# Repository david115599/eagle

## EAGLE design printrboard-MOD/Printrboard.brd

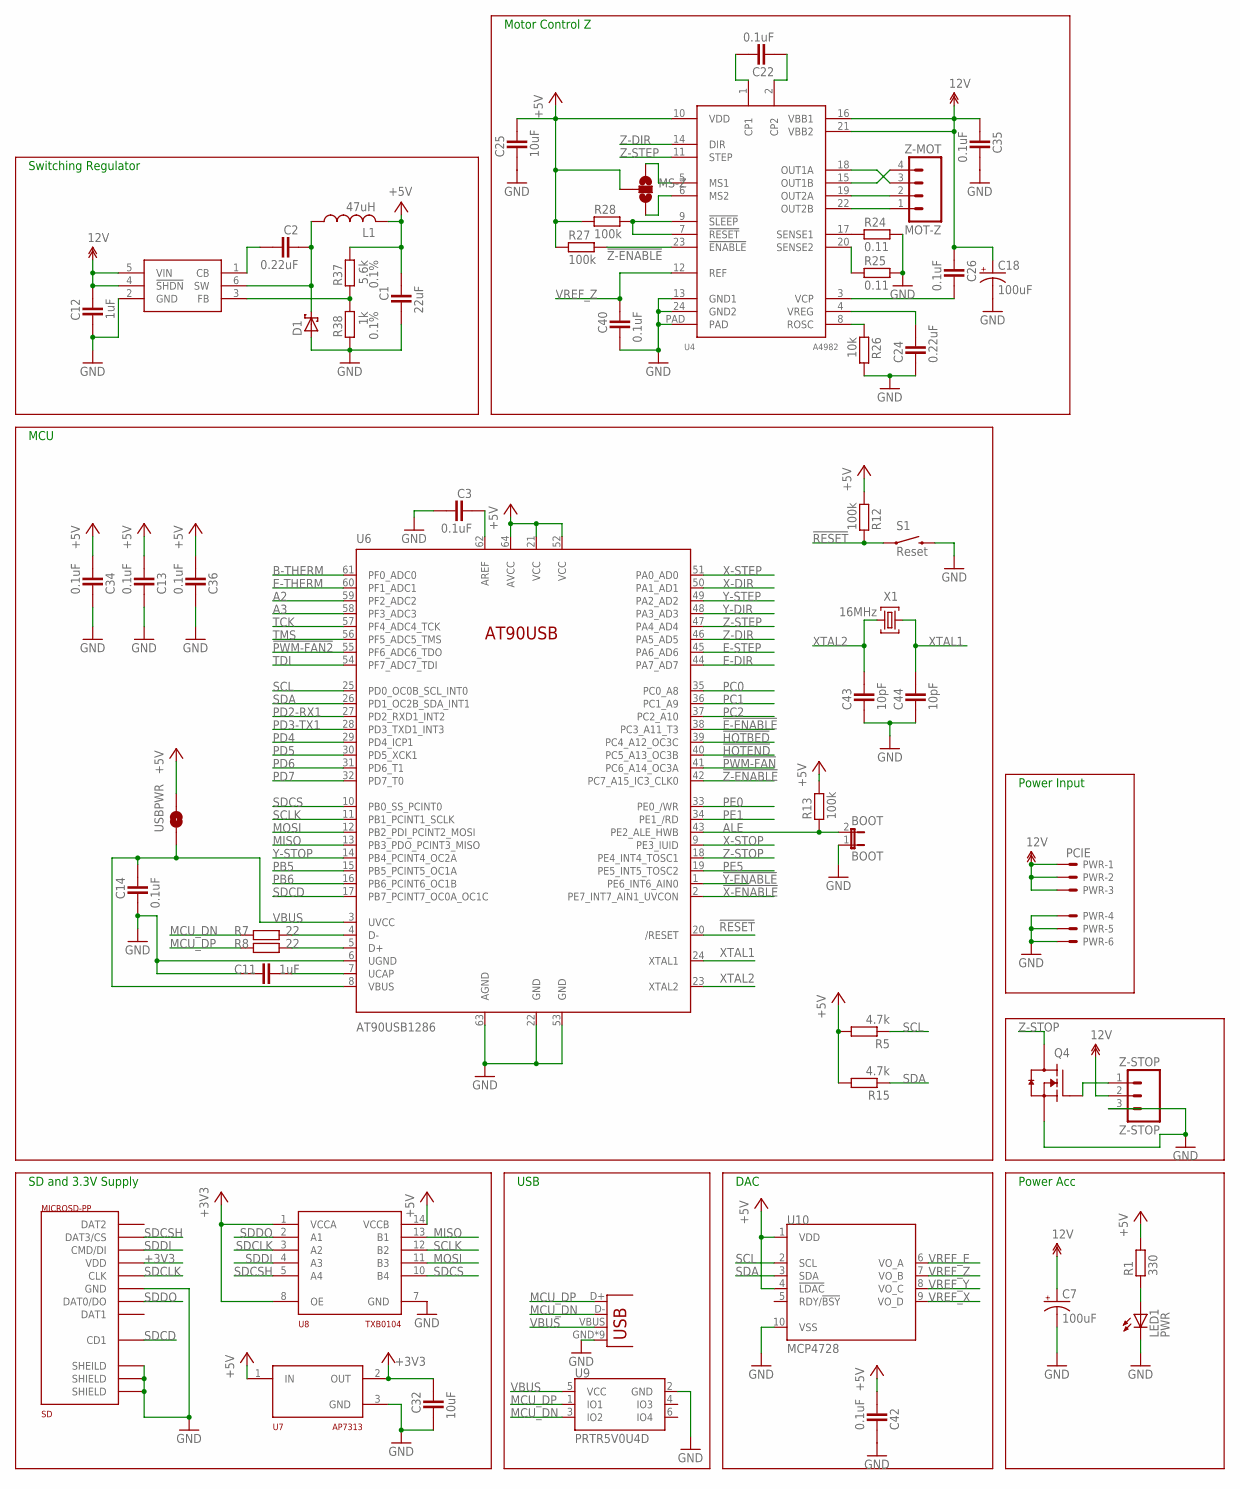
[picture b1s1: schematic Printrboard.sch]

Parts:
BOOT: BOOT; 1X02; MPN 640452-2
C1: 22uF; CAPC2012X145AN; MPN GRT21BR60J226ME13L
C2, C24: 0.22uF; CAPC2012X145AN
C3, C13, C14, C22, C26, C34, C35, C36, C40, C42: 0.1uF; CAPC2012X145AN
C7, C18: 100uF; PANASONIC_D
C11, C12: 1uF; CAPC2012X145AN
C25, C32: 10uF; CAPC2012X145AN
C43, C44: 10pF; CAPC2012X145AN
D1: SCH-DIODESMA; SMA
L1: 47uH; SDR1006
LED1: PWR; CHIP-LED0805
MS-Z: SOLDERJUMPER_2WAYCONNECTED; SJ_3_CONNECTED
PWR: PCIE; 5566-6
Q4: RFP30N06LE; SOT95P280X135-3N
R1: 330; RESC2012X70N
R5, R15: 4.7k; RESC2012X70N
R7, R8: 22; RESC2012X70N
R12, R13, R27, R28: 100k; RESC2012X70N
R24, R25: 0.11; RESC2012X70N
R26: 10k; RESC2012X70N
R37: 5.6k; RESC2012X70N; TOLERANCE 0.1%
R38: 1k; RESC2012X70N; TOLERANCE 0.1%
S1: Reset; TACTILE_SWITCH_TALL
SD: MICROSD-PP; USD-101-00660-68-6
U1: LM2841; TSOT6
U4: A4982; TSSOP-24
U6: AT90USB1286; TQFP64-2
U7: AP7313; SOT23C
U8: TXB0104; TSSOP14
U9: PRTR5V0U4D; SOT23-6
U10: MCP4728; MSOP10
USB-M: USB-MICRO-PTH; USB-MICROB-PTH
USBPWR: SOLDERJUMPERNO; SJ_2S-NO
X1: 16MHz; NDK-XTAL
Z-MOT: MOT-Z; MOLEX-1X4
Z-STOP: Z-STOP; MOLEX-1X3

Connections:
12V: C7.+, C12.1, C18.+, C26.1, C35.1, PWR.1, PWR.2, PWR.3, U1.4 (!SHDN), U1.5 (VIN), U4.16 (VBB1), U4.21 (VBB2), Z-STOP.2
!E-ENABLE: U6.38 (PC3_A11_T3)
!HOTBED: U6.39 (PC4_A12_OC3C)
!HOTEND: U6.40 (PC5_A13_OC3B)
!PWM-FAN: U6.41 (PC6_A14_OC3A)
!PWM-FAN2: U6.55 (PF6_ADC6_TDO)
!RESET: R12.1, S1.A2 (1), U6.20 (/RESET)
!X-ENABLE: U6.2 (PE7_INT7_AIN1_UVCON)
!Y-ENABLE: U6.1 (PE6_INT6_AIN0)
!Z-ENABLE: R27.2, U4.23 (!ENABLE), U6.42 (PC7_A15_IC3_CLK0)
+3V3: C32.1, SD.P$4 (VDD), U7.2 (OUT), U8.1 (VCCA), U8.8 (OE)
+5V: C1.1, C13.2, C25.2, C34.2, C36.2, C42.2, L1.P$2 (2), MS-Z.2, R1.2, R5.2, R12.2, R13.2, R15.2, R27.1, R28.1, R37.1, U4.10 (VDD), U6.21 (VCC), U6.52 (VCC), U6.64 (AVCC), U7.1 (IN), U8.14 (VCCB), U10.1 (VDD), U10.4 (!LDAC), USBPWR.2
A2: U6.59 (PF2_ADC2)
A3: U6.58 (PF3_ADC3)
ALE: BOOT.2, R13.1, U6.43 (PE2_ALE_HWB)
AREF: C3.1, U6.62 (AREF)
B-THERM: U6.61 (PF0_ADC0)
E-DIR: U6.44 (PA7_AD7)
E-STEP: U6.45 (PA6_AD6)
E-THERM: U6.60 (PF1_ADC1)
GND: BOOT.1, C1.2, C3.2, C7.-, C11.1, C12.2, C13.1, C14.2, C18.-, C24.1, C25.1, C32.2, C34.1, C35.2, C36.1, C40.2, C42.1, C43.1, C44.1, D1.A, LED1.C, PWR.4, PWR.5, PWR.6, Q4.2 (S), R24.2, R25.2, R26.2, R38.2, S1.B2 (2), SD.GND1 (SHEILD), SD.GND2 (SHIELD), SD.GND3 (SHIELD), SD.P$6 (GND), U1.2 (GND), U4.13 (GND1), U4.24 (GND2), U4.PAD, U6.6 (UGND), U6.22 (GND), U6.53 (GND), U6.63 (AGND), U7.3 (GND), U8.7 (GND), U9.2 (GND), U10.10 (VSS), USB-M.GND, USB-M.GND1 (GND), USB-M.GND2 (GND), USB-M.GND3 (GND), USB-M.GND4 (GND), USB-M.GND5 (GND), USB-M.GND6 (GND), USB-M.GND7 (GND), USB-M.GND8 (GND), Z-STOP.3
MCU_DN: R7.1, U9.3 (IO2), USB-M.D-
MCU_DP: R8.1, U9.1 (IO1), USB-M.D+
MISO: U6.13 (PB3_PDO_PCINT3_MISO), U8.13 (B1)
MOSI: U6.12 (PB2_PDI_PCINT2_MOSI), U8.11 (B3)
unnamed: LED1.A, R1.1
unnamed: R7.2, U6.4 (D-)
unnamed: R8.2, U6.5 (D+)
unnamed: Q4.1 (G), Z-STOP.1
unnamed: C11.2, U6.7 (UCAP)
unnamed: R37.2, R38.1, U1.3 (FB)
unnamed: U4.15 (OUT1B), Z-MOT.4
unnamed: U4.18 (OUT1A), Z-MOT.3
unnamed: U4.19 (OUT2A), Z-MOT.2
unnamed: C22.2, U4.1 (CP1)
unnamed: C22.1, U4.2 (CP2)
unnamed: R24.1, U4.17 (SENSE1)
unnamed: R25.1, U4.20 (SENSE2)
unnamed: R26.1, U4.8 (ROSC)
unnamed: C24.2, U4.4 (VREG)
unnamed: R28.2, U4.7 (!RESET), U4.9 (!SLEEP)
unnamed: C26.2, U4.3 (VCP)
unnamed: U4.22 (OUT2B), Z-MOT.1
unnamed: MS-Z.1, U4.5 (MS1)
unnamed: MS-Z.3, U4.6 (MS2)
unnamed: C2.1, D1.C, L1.P$1 (1), U1.6 (SW)
unnamed: C2.2, U1.1 (CB)
PB5: U6.15 (PB5_PCINT5_OC1A)
PB6: U6.16 (PB6_PCINT6_OC1B)
PC0: U6.35 (PC0_A8)
PC1: U6.36 (PC1_A9)
PC2: U6.37 (PC2_A10)
PD2-RX1: U6.27 (PD2_RXD1_INT2)
PD3-TX1: U6.28 (PD3_TXD1_INT3)
PD4: U6.29 (PD4_ICP1)
PD5: U6.30 (PD5_XCK1)
PD6: U6.31 (PD6_T1)
PD7: U6.32 (PD7_T0)
PE0: U6.33 (PE0_/WR)
PE1: U6.34 (PE1_/RD)
PE5: U6.19 (PE5_INT5_TOSC2)
SCL: R5.1, U6.25 (PD0_OC0B_SCL_INT0), U10.2 (SCL)
SCLK: U6.11 (PB1_PCINT1_SCLK), U8.12 (B2)
SDA: R15.1, U6.26 (PD1_OC2B_SDA_INT1), U10.3 (SDA)
SDCD: SD.CD (CD1), U6.17 (PB7_PCINT7_OC0A_OC1C)
SDCLK: SD.P$5 (CLK), U8.3 (A2)
SDCS: U6.10 (PB0_SS_PCINT0), U8.10 (B4)
SDCSH: SD.P$2 (DAT3/CS), U8.5 (A4)
SDDI: SD.P$3 (CMD/DI), U8.4 (A3)
SDDO: SD.P$7 (DAT0/DO), U8.2 (A1)
TCK: U6.57 (PF4_ADC4_TCK)
TDI: U6.54 (PF7_ADC7_TDI)
TMS: U6.56 (PF5_ADC5_TMS)
VBUS: C14.1, U6.3 (UVCC), U6.8 (VBUS), U9.5 (VCC), USB-M.VBUS, USBPWR.1
VREF_E: U10.6 (VO_A)
VREF_X: U10.9 (VO_D)
VREF_Y: U10.8 (VO_C)
VREF_Z: C40.1, U4.12 (REF), U10.7 (VO_B)
X-DIR: U6.50 (PA1_AD1)
X-STEP: U6.51 (PA0_AD0)
X-STOP: U6.9 (PE3_IUID)
XTAL1: C44.2, U6.24 (XTAL1), X1.P$1 (1)
XTAL2: C43.2, U6.23 (XTAL2), X1.P$2 (2)
Y-DIR: U6.48 (PA3_AD3)
Y-STEP: U6.49 (PA2_AD2)
Y-STOP: U6.14 (PB4_PCINT4_OC2A)
Z-DIR: U4.14 (DIR), U6.46 (PA5_AD5)
Z-STEP: U4.11 (STEP), U6.47 (PA4_AD4)
Z-STOP: Q4.3 (D), U6.18 (PE4_INT4_TOSC1)

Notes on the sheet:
Motor Control Z
Power Acc
Switching Regulator
SD and 3.3V Supply
Power Input
MCU
USB
DAC

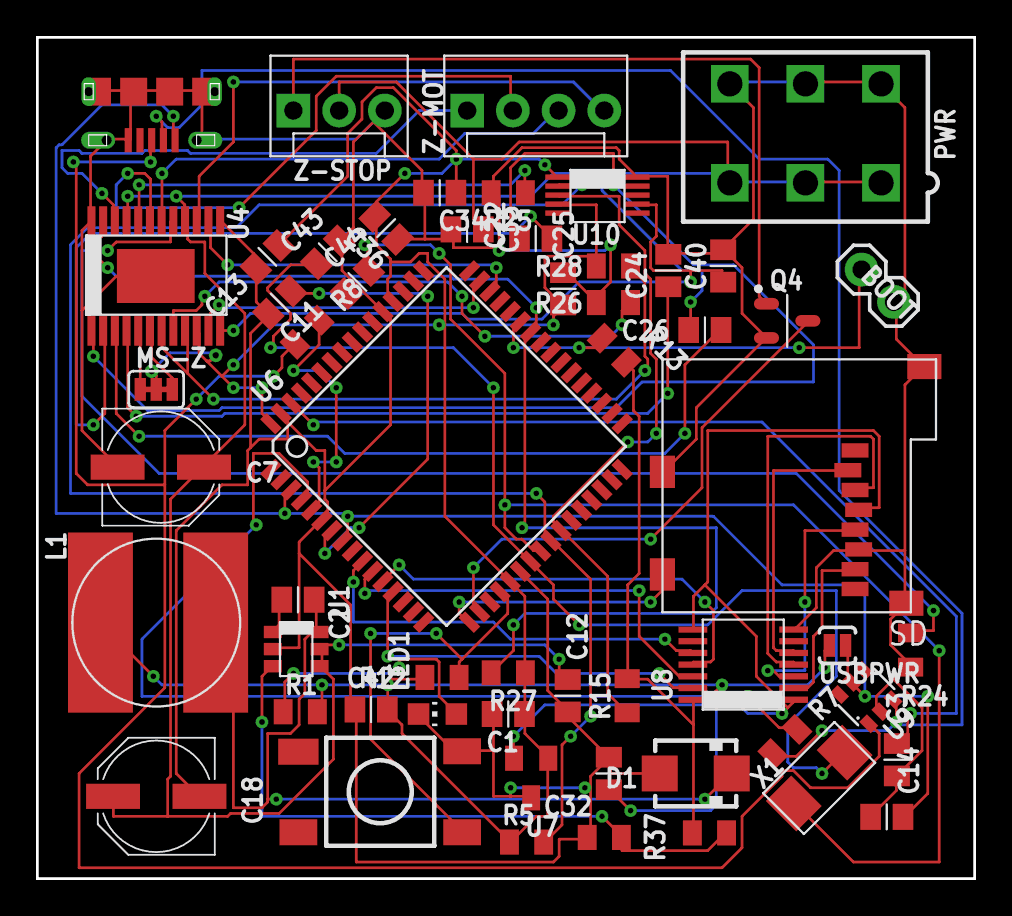
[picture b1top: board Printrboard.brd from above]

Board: 4 copper layers, 52.1 x 46.7 mm, 56 parts (0 on the bottom side), 50 nets.

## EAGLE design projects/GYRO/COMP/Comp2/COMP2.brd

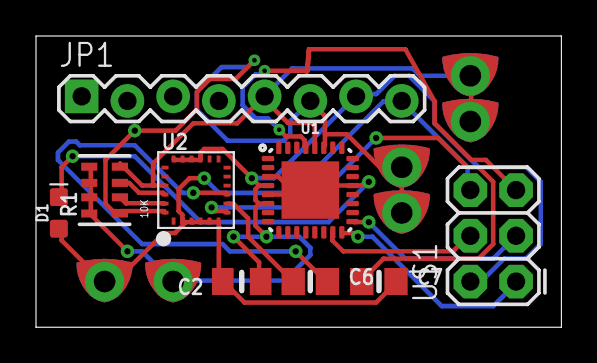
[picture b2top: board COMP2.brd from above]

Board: 2 copper layers, 29.2 x 16.2 mm, 15 parts (0 on the bottom side), 14 nets.

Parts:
C2: 10µF; 0805_10MGAP
C6: 0.22uF; 0805-NO
C7: 10uF; 0805-NO
D1: BLUE; LED-0603
GND: SEWTAP0.5IN; SEWINGTAP_0.5
JP1: 1X08_LOCK
R1: 10K; RESPACK_4X0603
SCL1, SCL2: SEWTAP0.5IN; SEWINGTAP_0.5
SDA1, SDA2: SEWTAP0.5IN; SEWINGTAP_0.5
U1: MLF32-PAD
U2: LSM9DS0TR; LGA24_4X4MM
U$1: AVR_SPI_PRG_6PTH; 2X3
VCC: SEWTAP0.5IN; SEWINGTAP_0.5

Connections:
GND: C2.2, C7.2, D1.A, GND.TAP, JP1.8, U2.2, U2.3, U2.4, U2.5, U2.6, U$1.6
MISO: U1.16, U$1.1
MOSI: U1.15, U$1.4
unnamed: C6.1, U2.8
unnamed: C6.2, U2.9
unnamed: D1.C, U1.3, U1.5, U1.21, U1.PAD
unnamed: C7.1, U2.7
RESET: U1.29, U$1.5
SA0_G: R1.3, U2.22
SA0_XM: R1.2, U2.23
SCK: U1.17, U$1.3
SCL: JP1.5, R1.4, SCL1.TAP, SCL2.TAP, U1.28, U2.21
SDA: JP1.6, R1.1, SDA1.TAP, SDA2.TAP, U1.27, U2.24
VCC: C2.1, JP1.7, R1.5, R1.6, R1.7, R1.8, U1.4, U1.6, U2.15, U2.16, U2.17, U2.18, U$1.2, VCC.TAP

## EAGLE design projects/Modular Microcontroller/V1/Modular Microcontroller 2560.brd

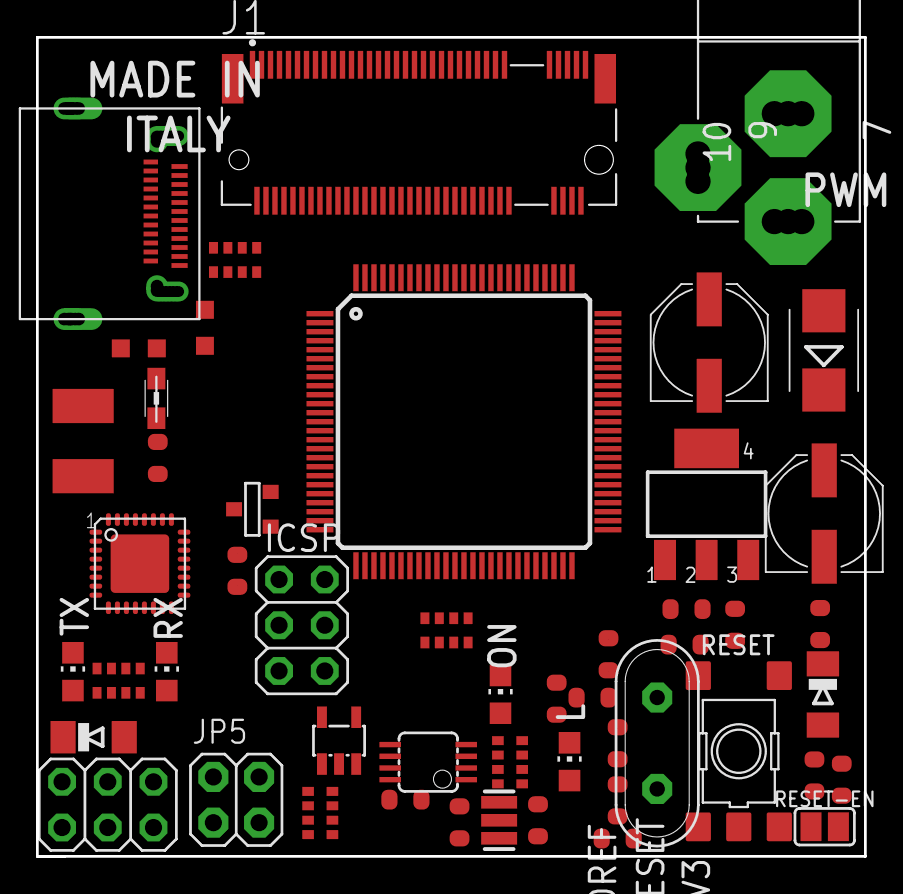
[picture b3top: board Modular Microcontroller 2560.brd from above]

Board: 2 copper layers, 46.0 x 45.5 mm, 52 parts (1 on the bottom side), 48 nets, no tracks yet.

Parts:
C1, C14, C15: 22p; C0603-ROUND
C2, C3, C4, C5, C6, C7, C8, C9, C11, C12: 100n; C0603-ROUND
C10, C13: 1u; C0603-ROUND
D1: M7; SMB
D2, D3: CD1206-S01575; MINIMELF
F1: MF-MSMF050-2 500mA; L1812
GROUND: SJ
IC1: NCP1117ST50T3G; SOT223
IC3: ATMEGA2560-16AU; TQFP100
IC4: ATMEGA16U2-MU; MLF32
IC6: LP2985-33DBVR; SOT23-DBV
IC7: LMV358IDGKR; MSOP08
ICSP, ICSP1: 3x2M; 2X03
J1: 1-2199119-3; TE_1-2199119-3
JP5: 2x2M - NM; 2X02
L: YELLOW; CHIP-LED0805
L1: BLM21; 0805
ON: GREEN; CHIP-LED0805
PC1, PC2: 47u; PANASONIC_D
R1, R2: 1M; R0603-ROUND
RESET: TS42031-160R-TR-7260; TS42
RESET-EN: SJ
RN1, RN5: 10K; CAT16
RN2: 22R; CAY16
RN3, RN4: 1k; CAY16
RX: YELLOW; CHIP-LED0805
T1: FDN340P; SOT-23
TX: YELLOW; CHIP-LED0805
U$2: USB-TYPE-C; USB-TYPE-C-SMT
X1: POWERSUPPLY_DC21MMX; POWERSUPPLY_DC-21MM
Y1: CSTCE16M0V53-R0 16MHZ; RESONATOR
Y2: 16MHz; QS
Z1, Z2: CG0603MLC-05E; CT/CN0603

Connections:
8PB4: IC4.18, JP5.1
8PB5: IC4.19, JP5.3
8PB6: IC4.20, JP5.2
8PB7: IC4.21, JP5.4
+3V3: C13.2, IC6.5, IC7.6
+5V: C4.1, C5.1, C6.1, C9.1, C11.2, D2.C, D3.C, IC1.2, IC1.4, IC3.10, IC3.31, IC3.61, IC3.80, IC3.100, IC4.4, IC4.32, IC6.1, IC6.3, IC7.8, ICSP.2, ICSP1.2, PC2.+, RN1.6, RN1.7, RN3.1, RN4.5, RN4.6, RN5.2, RN5.8, T1.2
AREF: C3.1, IC3.98
CMP: C12.2, IC7.5, RN5.3, RN5.5
D+: RN2.5, U$2.6, U$2.B6, Z2.2
D-: RN2.8, U$2.7, U$2.B7, Z1.2
DTR: C7.1, IC4.13, RN3.4
GATE_CMD: IC7.7, T1.3
GND: C1.2, C2.2, C3.2, C4.2, C5.2, C6.2, C8.2, C9.2, C11.1, C12.1, C13.1, C14.2, C15.2, GROUND.2, IC1.1, IC3.11, IC3.32, IC3.62, IC3.81, IC3.99, IC4.3, IC4.33, IC6.2, IC7.4, ICSP.6, ICSP1.6, L.C, ON.C, PC1.-, PC2.-, RESET.1, RESET.2, RN3.5, RN5.4, X1.1, X1.3, Y1.2
L13: IC7.1, IC7.2, RN3.7
M8RXD: IC4.9, RN4.7
M8TXD: IC4.8, RN4.8
MISO2: IC4.17, ICSP1.1
MOSI2: IC4.16, ICSP1.4
unnamed: L.A, RN3.2
unnamed: ON.A, RN3.8
unnamed: RN4.4, RX.A
unnamed: RN4.3, TX.A
PB1: IC3.20, ICSP.3
PB2: IC3.21, ICSP.4
PB3: IC3.22, ICSP.1
PB7: IC3.26, IC7.3
PE0: IC3.2, RN4.2
PE1: IC3.3, RN4.1
PWRIN: D1.A, X1.2
RD+: IC4.29, RN2.4
RD-: IC4.30, RN2.1
RESET: C1.1, C7.2, D3.A, IC3.30, ICSP.5, RESET.3, RESET.4, RESET-EN.1, RESET-EN.2, RN5.1
RESET2: D2.A, IC4.24, ICSP1.5, RN5.7
RXL: IC4.10, RX.C
SCK2: IC4.15, ICSP1.3
SCL: IC3.43, RN1.2
SDA: IC3.44, RN1.3
TXL: IC4.11, TX.C
UGND: C10.2, GROUND.1, IC4.28, L1.1, U$2.1, U$2.12, U$2.B1, U$2.B12
USBVCC: C8.1, F1.1, IC4.31, T1.1
USHIELD: L1.2, U$2.P$1, U$2.P$2, U$2.P$3, U$2.P$4, U$2.P$5, U$2.P$6, U$2.P$7, U$2.P$8, U$2.P$9, U$2.P$10, U$2.P$11, U$2.P$12, U$2.P$13, U$2.P$14, U$2.P$15, U$2.P$16, U$2.P$17, U$2.P$18, U$2.P$19, U$2.P$20, U$2.P$21, U$2.P$22, U$2.P$23, U$2.P$24, U$2.P$25, U$2.P$26, U$2.P$27, U$2.P$28, Z1.1, Z2.1
VBUS: F1.2, U$2.4, U$2.9, U$2.B4, U$2.B9
VIN: C2.1, D1.C, IC1.3, PC1.+, RN5.6
VUCAP: C10.1, IC4.27
XT1: C14.1, IC4.1, R2.1, Y2.2
XT2: C15.1, IC4.2, R2.2, Y2.1
XTAL1: IC3.34, R1.1, Y1.3
XTAL2: IC3.33, R1.2, Y1.1

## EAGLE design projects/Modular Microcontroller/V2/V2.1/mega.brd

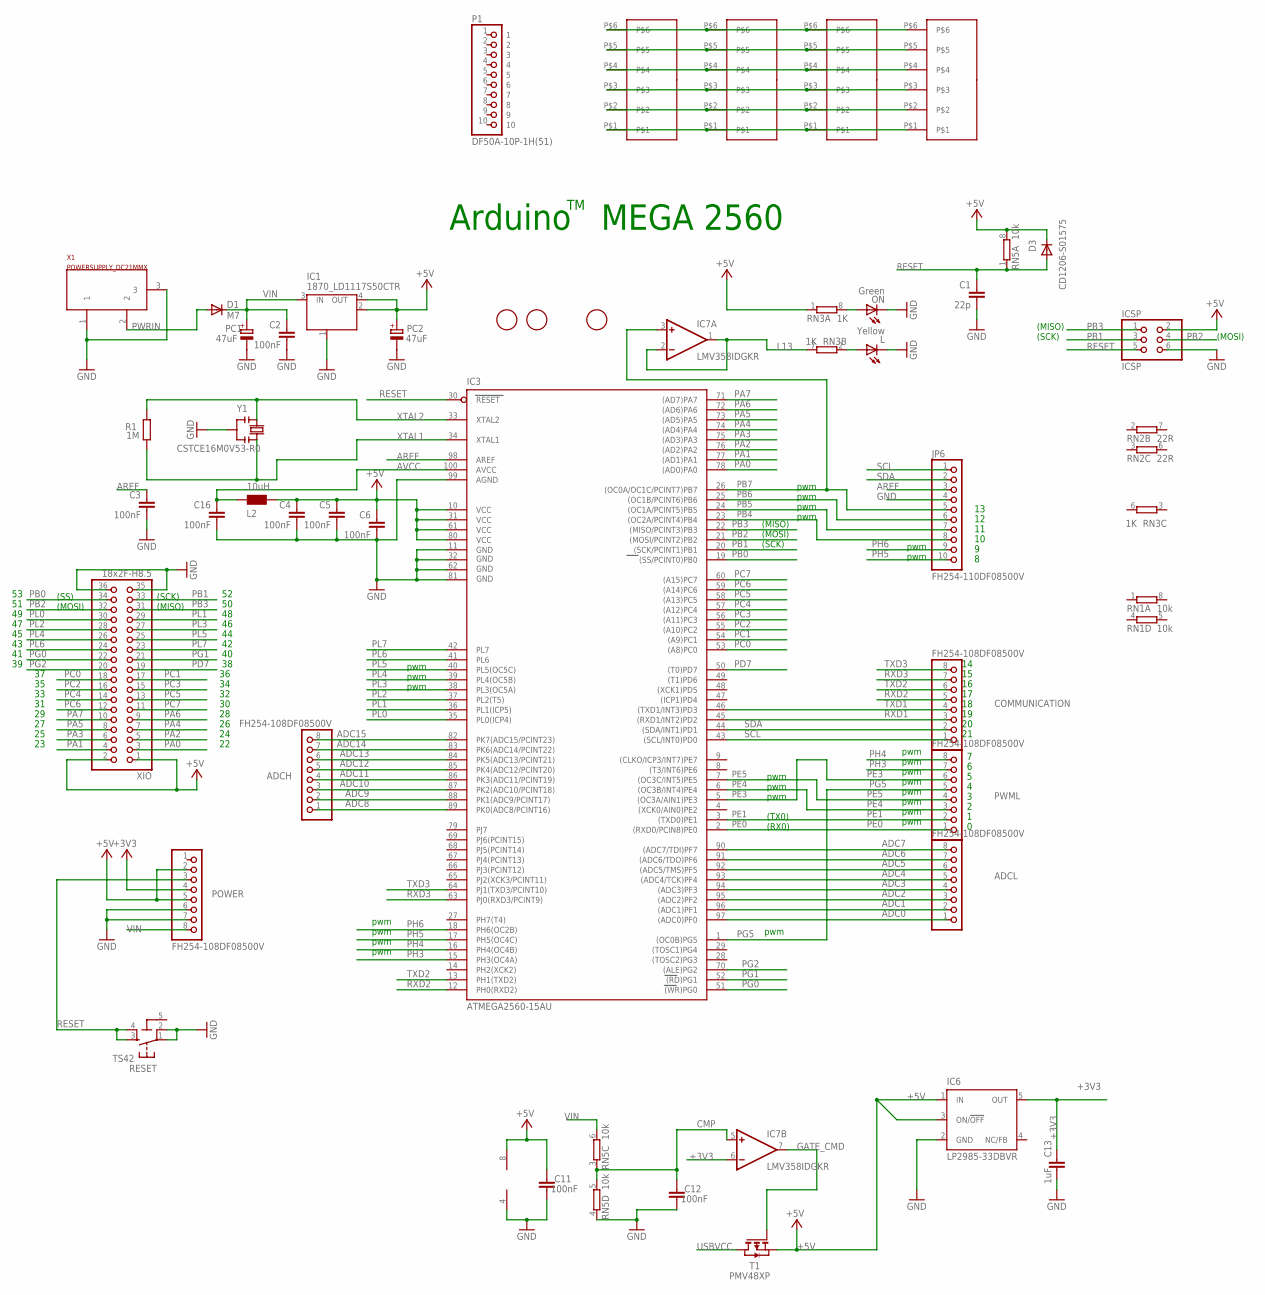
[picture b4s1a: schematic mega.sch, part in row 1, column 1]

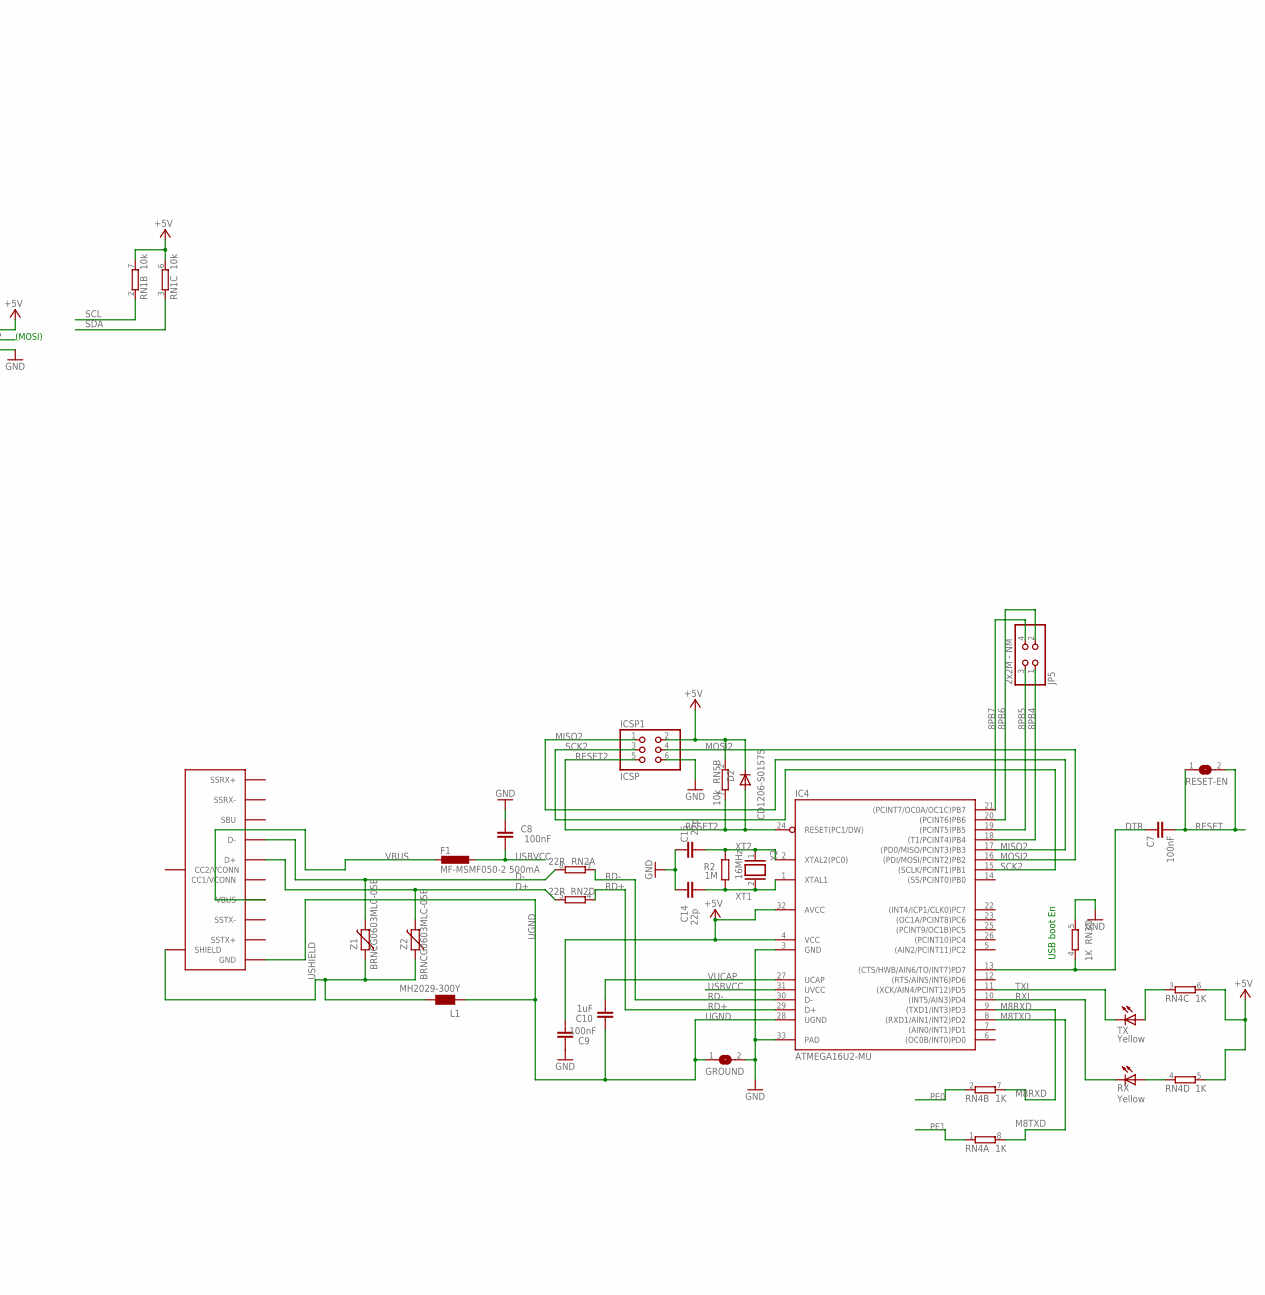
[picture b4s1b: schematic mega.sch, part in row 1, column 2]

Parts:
ADCH: FH254-108DF08500V; 1X08
ADCL: FH254-108DF08500V; 1X08
C1, C14, C15: 22p; C0603-ROUND
C2, C3, C4, C5, C6, C7, C8, C9, C11, C12, C16: 100nF; C0603-ROUND
C10, C13: 1uF; C0603-ROUND
COMMUNICATION: FH254-108DF08500V; 1X08
D1: M7; SMB
D2, D3: CD1206-S01575; MINIMELF
F1: MF-MSMF050-2 500mA; L1812
FD1, FD2, FD4: FIDUCIALMOUNT; FIDUCIA-MOUNT
GROUND: SJ
IC1: 1870_LD1117S50CTR; LINEAR_SOT223
IC3: ATMEGA2560-15AU; TQFP100
IC4: ATMEGA16U2-MU; MLF32
IC6: LP2985-33DBVR; SOT23-DBV
IC7: LMV358IDGKR; MSOP08
ICSP, ICSP1: ICSP; 2X03
JP5: 2x2M - NM; 2X02
JP6: FH254-110DF08500V; 1X10
L: Yellow; CHIPLED_0805
L1: MH2029-300Y; 0805
L2: 10uH; 0805
ON: Green; CHIPLED_0805
P1: DF50A-10P-1H(51); HRS_DF50A-10P-1H(51)
PC1, PC2: 47uF; PANASONIC_D
POWER: FH254-108DF08500V; 1X08
PWML: FH254-108DF08500V; 1X08
R1, R2: 1M; R0603-ROUND
RESET: TS42
RESET-EN: SJ
RN1, RN5: 10k; CAY16
RN2: 22R; CAY16
RN3, RN4: 1K; CAY16
RX: Yellow; CHIPLED_0805
T1: PMV48XP; SOT-23; PART_NUMBER PMV48XP
TX: Yellow; CHIPLED_0805
U$1: USB-TYPE-C; USB-TYPE-C-SMT
U$2, U$3, U$4, U$5: 6PINHERM; 6PINHERMSMD
X1: POWERSUPPLY_DC21MMX; POWERSUPPLY_DC-21MM
XIO: 18x2F-H8.5; 2X18
Y1: CSTCE16M0V53-R0; RESONATOR
Y2: 16MHz; QS
Z1, Z2: BRNCG0603MLC-05E; CT/CN0603

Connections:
5-GND: RESET.5 (5-GND)
8PB4: IC4.18 ((T1/PCINT4)PB4), JP5.1
8PB5: IC4.19 ((PCINT5)PB5), JP5.3
8PB6: IC4.20 ((PCINT6)PB6), JP5.2
8PB7: IC4.21 ((PCINT7/OC0A/OC1C)PB7), JP5.4
+3V3: C13.2, IC6.5 (OUT), IC7.6 (-IN), POWER.4
+5V: C4.1, C5.1, C6.1, C9.1, C11.2, D2.C, D3.C, IC1.2 (OUT), IC1.4 (OUT), IC3.10 (VCC), IC3.31 (VCC1), IC3.61 (VCC2), IC3.80 (VCC3), IC4.4 (VCC), IC4.32 (AVCC), IC6.1 (IN), IC6.3 (ON/!OFF), IC7.8 (V+), ICSP.2, ICSP1.2, L2.2, PC2.+, POWER.2, POWER.5, RN1.6 (2), RN1.7 (2), RN3.1, RN4.5 (2), RN4.6 (2), RN5.2 (1), RN5.8 (2), T1.2 (S), XIO.1, XIO.2
ADC0: ADCL.1, IC3.97 ((ADC0)PF0)
ADC1: ADCL.2, IC3.96 ((ADC1)PF1)
ADC2: ADCL.3, IC3.95 ((ADC2)PF2)
ADC3: ADCL.4, IC3.94 ((ADC3)PF3)
ADC4: ADCL.5, IC3.93 ((ADC4/TCK)PF4)
ADC5: ADCL.6, IC3.92 ((ADC5/TMS)PF5)
ADC6: ADCL.7, IC3.91 ((ADC6/TDO)PF6)
ADC7: ADCL.8, IC3.90 ((ADC7/TDI)PF7)
ADC8: ADCH.1, IC3.89 (PK0(ADC8/PCINT16))
ADC9: ADCH.2, IC3.88 (PK1(ADC9/PCINT17))
ADC10: ADCH.3, IC3.87 (PK2(ADC10/PCINT18))
ADC11: ADCH.4, IC3.86 (PK3(ADC11/PCINT19))
ADC12: ADCH.5, IC3.85 (PK4(ADC12/PCINT20))
ADC13: ADCH.6, IC3.84 (PK5(ADC13/PCINT21))
ADC14: ADCH.7, IC3.83 (PK6(ADC14/PCINT22))
ADC15: ADCH.8, IC3.82 (PK7(ADC15/PCINT23))
AREF: C3.1, IC3.98 (AREF), JP6.3
AVCC: C16.1, IC3.100 (AVCC), L2.1
CMP: C12.2, IC7.5 (+IN), RN5.3 (1), RN5.5 (2)
D+: RN2.5 (2), U$1.6 (D+), U$1.B6 (D+), Z2.2
D-: RN2.8 (2), U$1.7 (D-), U$1.B7 (D-), Z1.2
DTR: C7.1, IC4.13 ((CTS/HWB/AIN6/TO/INT7)PD7), RN3.4 (1)
GATE_CMD: IC7.7 (OUT), T1.3 (G)
GND: C1.2, C2.2, C3.2, C4.2, C5.2, C6.2, C8.2, C9.2, C11.1, C12.1, C13.1, C14.2, C15.2, C16.2, GROUND.2, IC1.1 (GND/ADJ), IC3.11 (GND), IC3.32 (GND1), IC3.62 (GND2), IC3.81 (GND3), IC3.99 (AGND), IC4.3 (GND), IC4.33 (PAD), IC6.2 (GND), IC7.4 (V-), ICSP.6, ICSP1.6, JP6.4, L.C, ON.C, PC1.-, PC2.-, POWER.6, POWER.7, RESET.1, RESET.2, RN3.5 (2), RN5.4 (1), X1.1, X1.3, XIO.35, XIO.36, Y1.2
L13: IC7.1 (OUT), IC7.2 (-IN), RN3.7 (2)
M8RXD: IC4.9 ((TXD1/INT3)PD3), RN4.7 (2)
M8TXD: IC4.8 ((RXD1/AIN1/INT2)PD2), RN4.8 (2)
MISO2: IC4.17 ((PD0/MISO/PCINT3)PB3), ICSP1.1
MOSI2: IC4.16 ((PDI/MOSI/PCINT2)PB2), ICSP1.4
unnamed: U$2.P$6, U$3.P$6, U$4.P$6, U$5.P$6
unnamed: L.A, RN3.2 (1)
unnamed: ON.A, RN3.8 (2)
unnamed: U$2.P$5, U$3.P$5, U$4.P$5, U$5.P$5
unnamed: U$2.P$4, U$3.P$4, U$4.P$4, U$5.P$4
unnamed: U$2.P$3, U$3.P$3, U$4.P$3, U$5.P$3
unnamed: U$2.P$2, U$3.P$2, U$4.P$2, U$5.P$2
unnamed: U$2.P$1, U$3.P$1, U$4.P$1, U$5.P$1
unnamed: RN4.4 (1), RX.A
unnamed: RN4.3 (1), TX.A
PA0: IC3.78 ((AD0)PA0), XIO.3
PA1: IC3.77 ((AD1)PA1), XIO.4
PA2: IC3.76 ((AD2)PA2), XIO.5
PA3: IC3.75 ((AD3)PA3), XIO.6
PA4: IC3.74 ((AD4)PA4), XIO.7
PA5: IC3.73 ((AD5)PA5), XIO.8
PA6: IC3.72 ((AD6)PA6), XIO.9
PA7: IC3.71 ((AD7)PA7), XIO.10
PB0: IC3.19 ((SS/PCINT0)PB0), XIO.34
PB1: IC3.20 ((SCK/PCINT1)PB1), ICSP.3, XIO.33
PB2: IC3.21 ((MOSI/PCINT2)PB2), ICSP.4, XIO.32
PB3: IC3.22 ((MISO/PCINT3)PB3), ICSP.1, XIO.31
PB4: IC3.23 ((OC2A/PCINT4)PB4), JP6.8
PB5: IC3.24 ((OC1A/PCINT5)PB5), JP6.7
PB6: IC3.25 ((OC1B/PCINT6)PB6), JP6.6
PB7: IC3.26 ((OC0A/OC1C/PCINT7)PB7), IC7.3 (+IN), JP6.5
PC0: IC3.53 ((A8)PC0), XIO.18
PC1: IC3.54 ((A9)PC1), XIO.17
PC2: IC3.55 ((A10)PC2), XIO.16
PC3: IC3.56 ((A11)PC3), XIO.15
PC4: IC3.57 ((A12)PC4), XIO.14
PC5: IC3.58 ((A13)PC5), XIO.13
PC6: IC3.59 ((A14)PC6), XIO.12
PC7: IC3.60 ((A15)PC7), XIO.11
PD7: IC3.50 ((T0)PD7), XIO.19
PE0: IC3.2 ((RXD0/PCIN8)PE0), PWML.1, RN4.2 (1)
PE1: IC3.3 ((TXD0)PE1), PWML.2, RN4.1
PE3: IC3.5 ((OC3A/AIN1)PE3), PWML.6
PE4: IC3.6 ((OC3B/INT4)PE4), PWML.3
PE5: IC3.7 ((OC3C/INT5)PE5), PWML.4
PG0: IC3.51 ((WR)PG0), XIO.22
PG1: IC3.52 ((RD)PG1), XIO.21
PG2: IC3.70 ((ALE)PG2), XIO.20
PG5: IC3.1 ((OC0B)PG5), PWML.5
PH3: IC3.15 (PH3(OC4A)), PWML.7
PH4: IC3.16 (PH4(OC4B)), PWML.8
PH5: IC3.17 (PH5(OC4C)), JP6.10
PH6: IC3.18 (PH6(OC2B)), JP6.9
PL0: IC3.35 (PL0(ICP4)), XIO.30
PL1: IC3.36 (PL1(ICP5)), XIO.29
PL2: IC3.37 (PL2(T5)), XIO.28
PL3: IC3.38 (PL3(OC5A)), XIO.27
PL4: IC3.39 (PL4(OC5B)), XIO.26
PL5: IC3.40 (PL5(OC5C)), XIO.25
PL6: IC3.41 (PL6), XIO.24
PL7: IC3.42 (PL7), XIO.23
PWRIN: D1.A, X1.2
RD+: IC4.29 (D+), RN2.4 (1)
RD-: IC4.30 (D-), RN2.1
RESET: C1.1, C7.2, D3.A, IC3.30 (RESET), ICSP.5, POWER.3, RESET.3, RESET.4, RESET-EN.1, RESET-EN.2, RN5.1
RESET2: D2.A, IC4.24 (RESET(PC1/DW)), ICSP1.5, RN5.7 (2)
RXD1: COMMUNICATION.3, IC3.45 ((RXD1/INT2)PD2)
RXD2: COMMUNICATION.5, IC3.12 (PH0(RXD2))
RXD3: COMMUNICATION.7, IC3.63 (PJ0(RXD3/PCINT9))
RXL: IC4.10 ((INT5/AIN3)PD4), RX.C
SCK2: IC4.15 ((SCLK/PCINT1)PB1), ICSP1.3
SCL: COMMUNICATION.1, IC3.43 ((SCL/INT0)PD0), JP6.1, RN1.2 (1)
SDA: COMMUNICATION.2, IC3.44 ((SDA/INT1)PD1), JP6.2, RN1.3 (1)
TXD1: COMMUNICATION.4, IC3.46 ((TXD1/INT3)PD3)
TXD2: COMMUNICATION.6, IC3.13 (PH1(TXD2))
TXD3: COMMUNICATION.8, IC3.64 (PJ1(TXD3/PCINT10))
TXL: IC4.11 ((XCK/AIN4/PCINT12)PD5), TX.C
UGND: C10.2, GROUND.1, IC4.28 (UGND), L1.1, U$1.1 (GND), U$1.12 (GND), U$1.B1 (GND), U$1.B12 (GND)
USBVCC: C8.1, F1.1, IC4.31 (UVCC), T1.1 (D)
USHIELD: L1.2, U$1.P$1 (SHIELD), U$1.P$2 (SHIELD), U$1.P$3 (SHIELD), U$1.P$4 (SHIELD), U$1.P$5 (SHIELD), U$1.P$6 (SHIELD), U$1.P$7 (SHIELD), U$1.P$8 (SHIELD), U$1.P$9 (SHIELD), U$1.P$10 (SHIELD), U$1.P$11 (SHIELD), U$1.P$12 (SHIELD), U$1.P$13 (SHIELD), U$1.P$14 (SHIELD), U$1.P$15 (SHIELD), U$1.P$16 (SHIELD), U$1.P$17 (SHIELD), U$1.P$18 (SHIELD), U$1.P$19 (SHIELD), U$1.P$20 (SHIELD), U$1.P$21 (SHIELD), U$1.P$22 (SHIELD), U$1.P$23 (SHIELD), U$1.P$24 (SHIELD), U$1.P$25 (SHIELD), U$1.P$26 (SHIELD), U$1.P$27 (SHIELD), U$1.P$28 (SHIELD), Z1.1, Z2.1
VBUS: F1.2, U$1.4 (VBUS), U$1.9 (VBUS), U$1.B4 (VBUS), U$1.B9 (VBUS)
VIN: C2.1, D1.C, IC1.3 (IN), PC1.+, POWER.8, RN5.6 (2)
VUCAP: C10.1, IC4.27 (UCAP)
XT1: C14.1, IC4.1 (XTAL1), R2.1, Y2.2
XT2: C15.1, IC4.2 (XTAL2(PC0)), R2.2, Y2.1
XTAL1: IC3.34 (XTAL1), R1.1, Y1.3
XTAL2: IC3.33 (XTAL2), R1.2, Y1.1

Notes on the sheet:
Arduino MEGA 2560
(SCK)
(MISO)
(MOSI)
pwm
(TX0)
(RX0)
(SS)
USB boot En

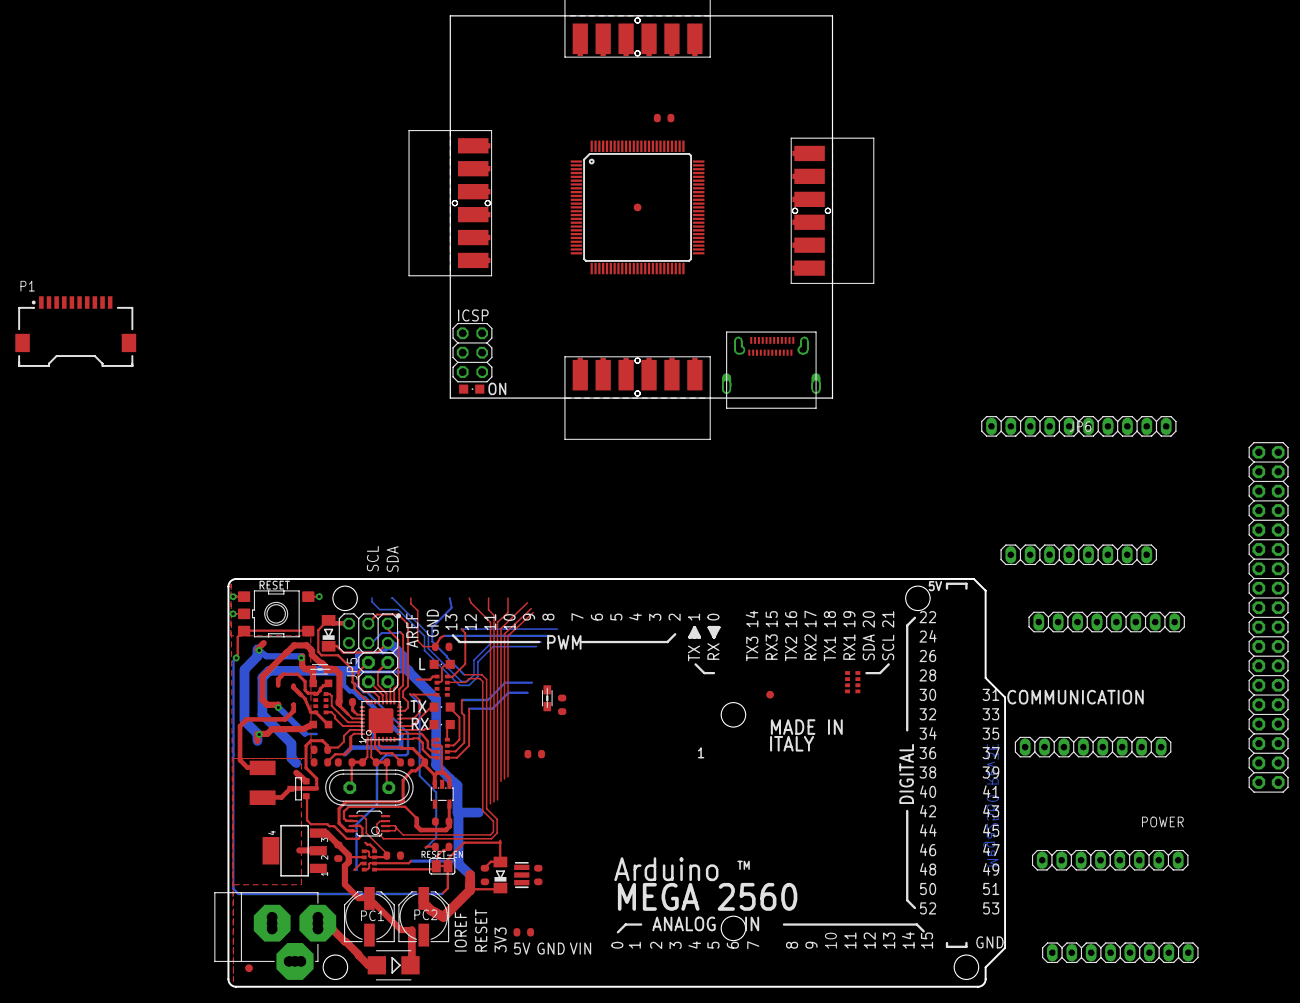
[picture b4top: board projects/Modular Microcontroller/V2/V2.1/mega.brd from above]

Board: 2 copper layers, 101.6 x 127.0 mm, 68 parts (1 on the bottom side), 117 nets.

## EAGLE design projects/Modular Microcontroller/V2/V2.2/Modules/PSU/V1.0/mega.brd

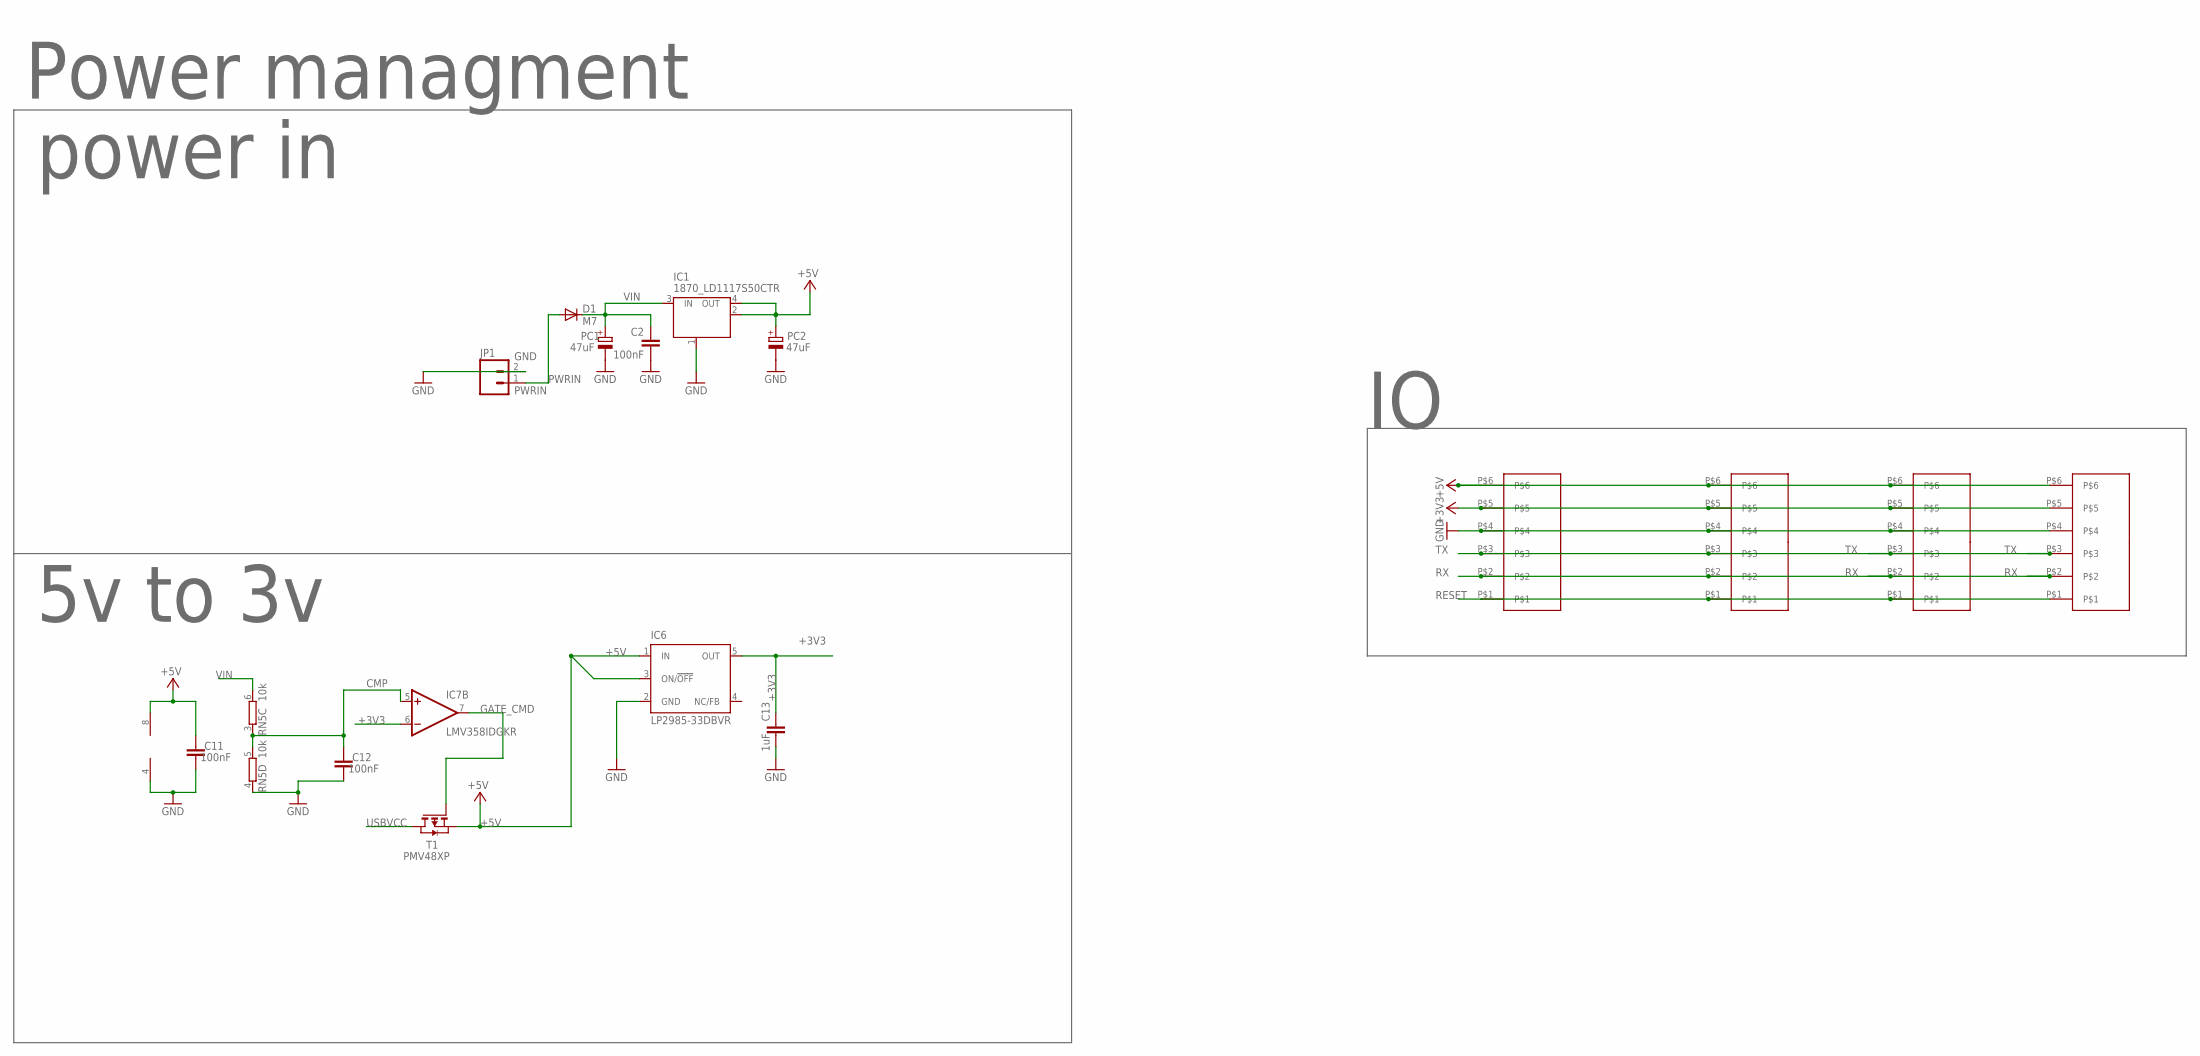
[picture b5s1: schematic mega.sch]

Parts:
C2, C11, C12: 100nF; C0603-ROUND
C13: 1uF; C0603-ROUND
D1: M7; SMB
IC1: 1870_LD1117S50CTR; LINEAR_SOT223
IC6: LP2985-33DBVR; SOT23-DBV
IC7: LMV358IDGKR; MSOP08
JP1: M02PTH; 1X02
PC1, PC2: 47uF; PANASONIC_D
RN5: 10k; CAY16
T1: PMV48XP; SOT-23; PART_NUMBER PMV48XP
U$1, U$3, U$6, U$7: 6PINHERM; 6PINHERMSMD

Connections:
+3V3: C13.2, IC6.5 (OUT), IC7.6 (-IN), U$1.P$5, U$3.P$5, U$6.P$5, U$7.P$5
+5V: C11.2, IC1.2 (OUT), IC1.4 (OUT), IC6.1 (IN), IC6.3 (ON/!OFF), IC7.8 (V+), PC2.+, T1.2 (S), U$1.P$6, U$3.P$6, U$6.P$6, U$7.P$6
CMP: C12.2, IC7.5 (+IN), RN5.3 (1), RN5.5 (2)
GATE_CMD: IC7.7 (OUT), T1.3 (G)
GND: C2.2, C11.1, C12.1, C13.1, IC1.1 (GND/ADJ), IC6.2 (GND), IC7.4 (V-), JP1.2, PC1.-, PC2.-, RN5.4 (1), U$1.P$4, U$3.P$4, U$6.P$4, U$7.P$4
PWRIN: D1.A, JP1.1
RESET: U$1.P$1, U$3.P$1, U$6.P$1, U$7.P$1
RX: U$1.P$2, U$3.P$2, U$6.P$2, U$7.P$2
TX: U$1.P$3, U$3.P$3, U$6.P$3, U$7.P$3
USBVCC: T1.1 (D)
VIN: C2.1, D1.C, IC1.3 (IN), PC1.+, RN5.6 (2)

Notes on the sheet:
Power managment
power in
5v to 3v

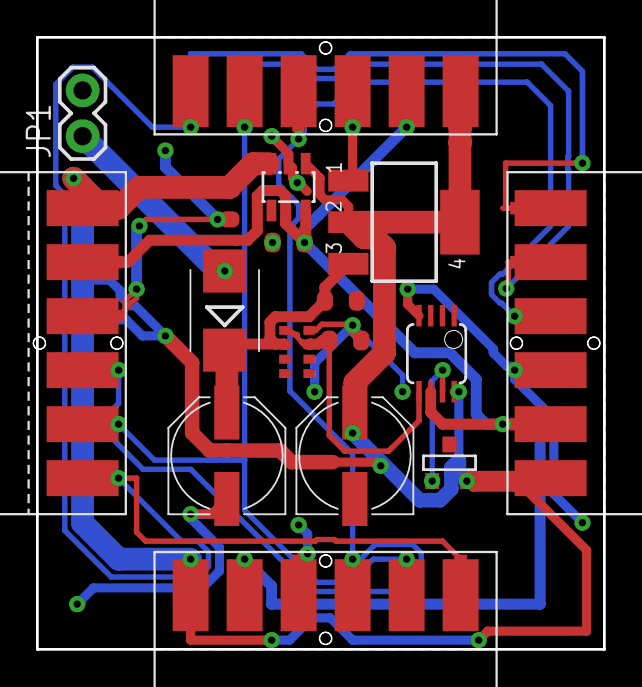
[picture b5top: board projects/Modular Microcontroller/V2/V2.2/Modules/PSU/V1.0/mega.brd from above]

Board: 2 copper layers, 31.5 x 34.0 mm, 17 parts (0 on the bottom side), 10 nets.

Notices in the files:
parts and their libraries:
microbuilder: This work is placed in the public domain, and may be freely used for commercial and non-commercial work with the following conditions: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
SparkFun-IC-Microcontroller: Licensing: Creative Commons ShareAlike 4.0 International - https://creativecommons.org/licenses/by-sa/4.0
